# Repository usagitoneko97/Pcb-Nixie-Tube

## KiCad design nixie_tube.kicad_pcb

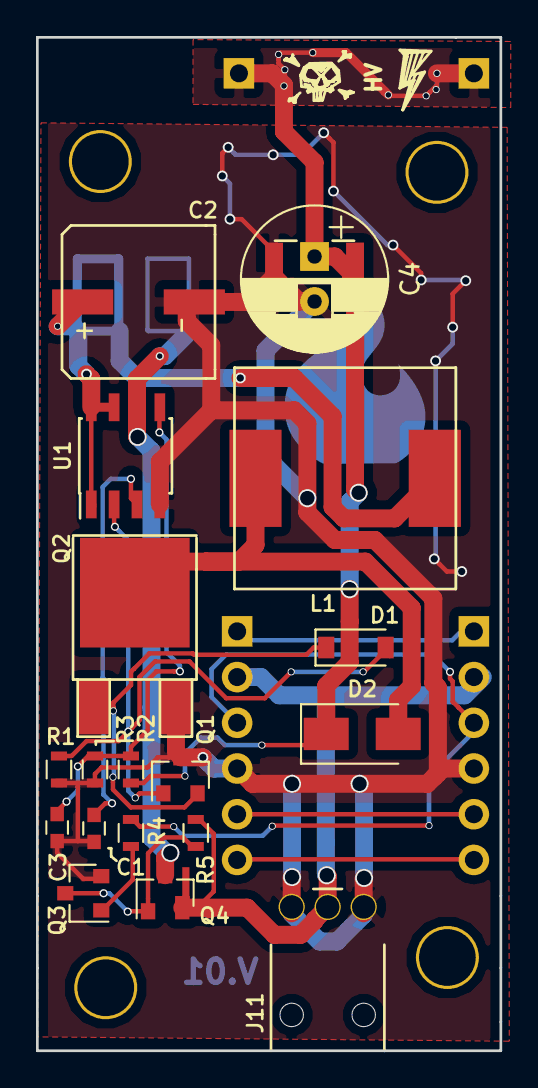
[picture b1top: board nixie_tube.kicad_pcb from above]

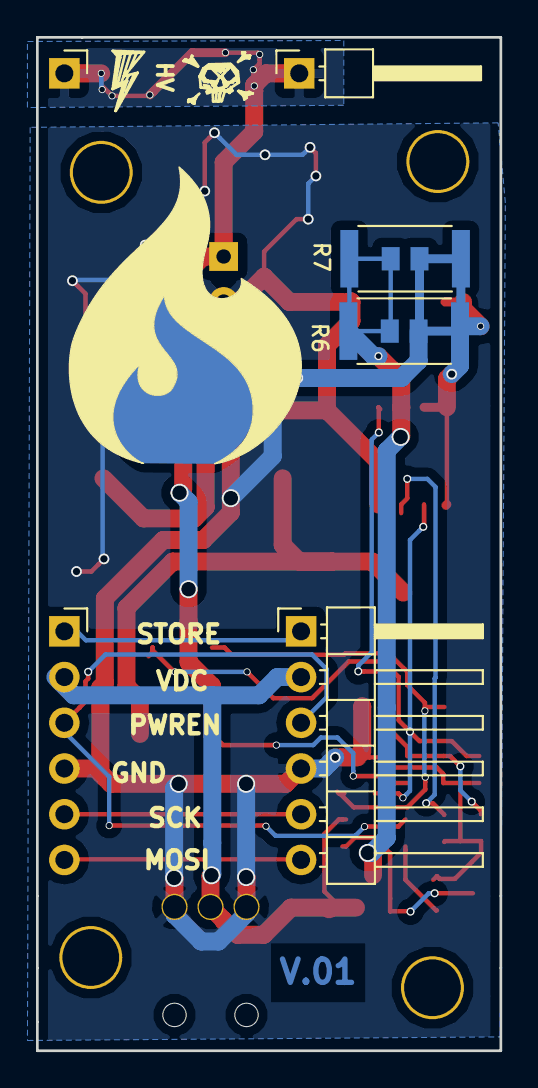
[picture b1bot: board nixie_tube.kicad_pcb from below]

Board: 2 copper layers, 25.8 x 56.3 mm, 29 parts (9 on the bottom side), 16 nets.

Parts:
C1: 10nF; C_0603
C2: 220uF; 220uF-35V-smd
C3: 0.01uF; C_0603
C4: 2.2uF; CP_RADIAL_and_mlcc
D1: 1N4148; D_SOD-123
D2: RS1M; D_SMA
Fire: G***; FireMeUpCopper
J1: Conn_01x06_Male; Socket_Strip_Angled_1x06_Pitch2.54mm_without_slikscreen
J2: Conn_01x06_Female; Pin_Header_Angled_1x06_Pitch2.54mm
J3: Conn_01x01_Male; Pin_Header_Angled_1x01_Pitch2.54mm
J4: Conn_01x01_Female; Socket_Strip_Angled_1x01_Pitch2.54mm_without_silkScreen
J11: dc003a; dc005a
L1: 220uH; 0630-10UH
Q1: SS8550; SOT-23
Q2: FQD5N60C; TO-252-2Lead
Q3: MMBTA42LT1; SOT-23
Q4: AO3407; SOT-23-alt_solder_on2_3
R1: 1k0; R_0603
R2: 470K; R_0603
R3: 3K; R_0603
R4, R5: R; R_0603
R6, R7: R; R_2512_0805
U1: MC34063; SOIC-8_3.9x4.9mm_Pitch1.27mm
Z?: lightning
Z?#2, Z?#4: skull
Z?#3: lightning

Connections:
+VDC: J1.2, J2.2, J11.1, Q4.2, R5.1
/MOSi: J1.6, J2.6
/PWREN: J1.3, J2.3, R4.2
/SCK: J1.5, J2.5
/STORE: J1.1, J2.1
GND: C1.2, C2.2, C3.2, C4.2, J1.4, J2.4, J11.2, J11.3, Q1.3, Q2.3, Q3.2, R1.2, R3.2, U1.4
unnamed: C1.1, U1.3
unnamed: C2.1, L1.1, R6.1, R7.1, U1.1, U1.7, U1.8
unnamed: C3.1, R2.2, R3.1, U1.5
unnamed: C4.1, D2.1, J3.1, J4.1, R2.1
unnamed: D1.1, Q1.2, Q2.1
unnamed: D1.2, Q1.1, R1.1, U1.2
unnamed: D2.2, L1.2, Q2.2
unnamed: Q3.1, R4.1
unnamed: Q3.3, Q4.1, R5.2
unnamed: Q4.3, R6.2, R7.2, U1.6

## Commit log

2017-10-04 added schematic for nixie power supply
2017-10-05 associate footprints into components
2017-10-07 placed all the trace
2017-10-07 modify schematic's footprint
2017-10-08 added DC-jack schematic
2017-10-08 created 4A inductor footprint, reorganize components
2017-10-09 created qs30-1 nixie tube footprint
2017-10-09 added pin headers for output
2017-10-11 added 220uF 35V smd footprint
2017-10-17 added 5 female and male pin headers at schematic
2017-10-17 finalize position of component
2017-10-17 rearrange components
2017-10-23 finished routed
2017-10-24 shrink the x size of the board
2017-10-24 finalize position of components
2017-10-24 Finish routing
2017-10-27 added and widen tracks of gnd and HV
2017-10-30 fixed pin headers placement
2017-11-05 moved partially to altium
2017-11-05 added missing files for altium
2017-11-06 arranged components on kicad
2017-11-06 verified pin placement of transistors with actual component
2017-11-06 placing components in altium
2017-11-07 finalize layout
2017-11-07 sync pin headers position with nixie tubes
2017-11-07 routed all including ground
2017-11-07 fixed pin position not in sequence with other board
2017-11-09 relocate space at top corner for 7mm pins
2017-11-09 readjust copper pour polygon dimension
2017-11-09 add extra mlcc footprint in cp radial fp
2017-11-13 reallocate space for 4 m3 pins
2017-11-14 move component away from each other, require rerout for some of them :|
2017-11-14 routed all remaining tracks
2017-11-15 shrink board by .5mm in x dir
2017-11-15 change m3 pins to no net
2017-11-15 fixed pin number not same with actual numbering of component
2017-11-15 extend ao3407 pad for making soldering easier when we dont want HV switching
2017-11-15 fixed pin position for ss8500
2017-11-15 fixed npn pin numbering not same with real device
2017-11-15 finalized everything
2017-11-16 fixed correct footprint for pin headers and socket, removed silk screen
2017-11-16 combined all into nixie-tube-merged
2017-11-16 move outline to f and b silk
2017-11-16 added panelizer folder project and panelized result
2017-11-17 added lightning and skull symbol together with edge cuts
2017-11-17 finalized tracks, added skull and lightning symbol
2017-11-17 finalized everything and ready to send out
2017-11-18 added via stiching around the board
2017-11-22 checked all components, modifed some tracks
2017-11-22 decrease label size, move HV symbol vertically up
2017-11-25 added fire symbol at the back of the board
2017-11-27 move the GND text away from via
